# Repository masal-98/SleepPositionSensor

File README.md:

## Sleep position classifier
## Objective

The aim of this group project was to develop a system able to correctly classify and forecast **12 specific sleep positions** (visible in the image above), using the data from **two accelerometers LIS3DH** placed one on the chest and one on the right ankle. 
The finished project includes: 
- development of the wearable device
- data acquisition
- data processing
- GUI for data sampling and visualization
- machine learning architecture able to perform sleep position classification

The PSoC communicates with the LIS3DH sensors using **I2C communication**, and the accelerometers have a sampling frequency set at 10Hz. 
The communication between the PSoC device and the pc was created using a **HC05 Bluetooth module** to make the device wearable.
Also, for wearability, the device is powered with a **9V battery** and a subsequent **9 to 5 voltage transformer**.
### Hardware
- 2 LIS3DH accelerometers
- 1 HC05 Bluetooth module
- 1 9V battery
- 1 9to5 voltage transformer
- 1 PSoC CY8CKIT-059 
- 1 breadboard
- 2 3D printed casings were used to encapsulate the accelerometers and place them on the body
- 10 2m long cables to connect the accelerometers to the PSoC
- 2 modular velcro bands to fix the accelerometers in place 

The links between the PSoC and the different components can be found in the dedicated folder in the form of the **hardware** **setup** documentation and the eagle schematic and board files.
The casing's 3D model can also be found in the dedicated folder.

### PSoC code
This section of code is responsible for I2C communication between the PSoC and the 2 accelerometers, which are sampling data with an ODR of 10Hz and are set on **FIFO mode**. The following code averages the 32 samples of the FIFO buffer from both accelerometers, each time they are simultaneously full.
Finally, the 6 averaged acceleration values (x, y and z from the chest and the ankle) are combined in a unique string and managed by the **UART** of the bluetooth module, having a baudrate of 9600 bps.

All code files of this section have been individually commented on for clarity.

### GUI code

This section of code deals with establishing a connection between pc and bluetooth module, visualizing the data sampled in real-time, and producing csv files following a specific sampling protocol, which are further used to train the machine learning module. 
It follows a description of the most important subsections of code, but the code has been commented throughout for clarity.
#### $Serial$ $interface$
This subsection is devoted to scanning all serial ports and creating a list used in the dropdown menu.
#### $Serial$ $Worker$
The **SerialWorker** class handles the connection with the bluetooth module by establishing a connection with the desired serial port (selectable in a drop down menu), reading data from this port from start (S) to end (E) tokens as soon as the Start button is pressed, **storing iteratively** the read lines in the data object and saving them at the end of the protocol in a single csv file.  
It's also responsible for sending char data on the serial port and closing the serial port before closing the app.
#### $Graphic$ $interface$ 
This sub-section of code deals with creating the **window** used by all the plot widgets and the various **buttons**. 
It's worth noting that the 6 data charts are plotted on the same window by first removing the oldest point, then adding the new one, and finally updating the data.
#### $Main$
The main is responsible for setting the **window size**, creating the **thread handler** and **initializing** all the **functions** previously mentioned.

### Machine Learning
#### $Install$

The Machine Learning portion of this project was created using a Jupyter Notebook.
The library used are available in the *requirements.txt* file inside the *machine learning folder* and any function needed is clearly listed and commented troughout the code.

#### $Data$
In order to run the code, it's necessary to upload the csv files produced by us during the sampling. All the paths are stored in a distinct variable.

The data consists in 11 csv files sampled from 11 different people, it's worth nothing that the file 'fabio_20220601_193018.csv' was discarted 
due to errors during the sampling procedure, thus we ended up with 10 different people, a sample size big enough to guarantee inter-subject variabilty.

The data available was studied in three different ways, in order to see if the accuracy of the model could be improved:
- **Raw** sampled data
- **Average** of data for each sensor
- **Average** of data for each sensor + **minimun and maximum** values for each sensor

#### $Data Preprocessing$
It's important to note that the **first 20 samples of each position recording were removed**, due to the patient still not being completely settled down and ready for the sampling. 
The data was also **normalized** as good practice dictates.

#### $Data Visualization$
The data was visualized multiple times, this allowed us to purge it from artifacts and anomalies and improve the learning algorithm, such as the *transient
data* between two positions mentioned in the previous paragraph.

#### $Features$
The data was gathered from 2 accelerometers, one on the chest and one on the right ankle. Therefore we have 6 inputs + 1 input for the subject's sex.
- x_chest
- y_chest
- z_chest
- x_ankle
- y_ankle
- z_ankle
- sex

#### $Target Variable$
The variable that we need to predict is the sleeping position. It can be one of twelve positions.

##### $Run$
To run the code, simply run sequentially every data cell. 
The code was tested on all three datasets, and the best performing one turned out to be the **Random Forest Classifier** learned using the **average+min_max** dataset, which reached **50% of accuracy** on the test set.

#### $Master Position$
In order to better assess the performance of the classifier we also tested it only on the four "master" positions: by grouping by three the positions (and therefore eliminating the small variations between each of the main positions) we obtained the **main positions**: supine, prone, left-sided and right-sided. 
When we tested our algorithm only with these targets, we easily obtained **100% accuracy**.

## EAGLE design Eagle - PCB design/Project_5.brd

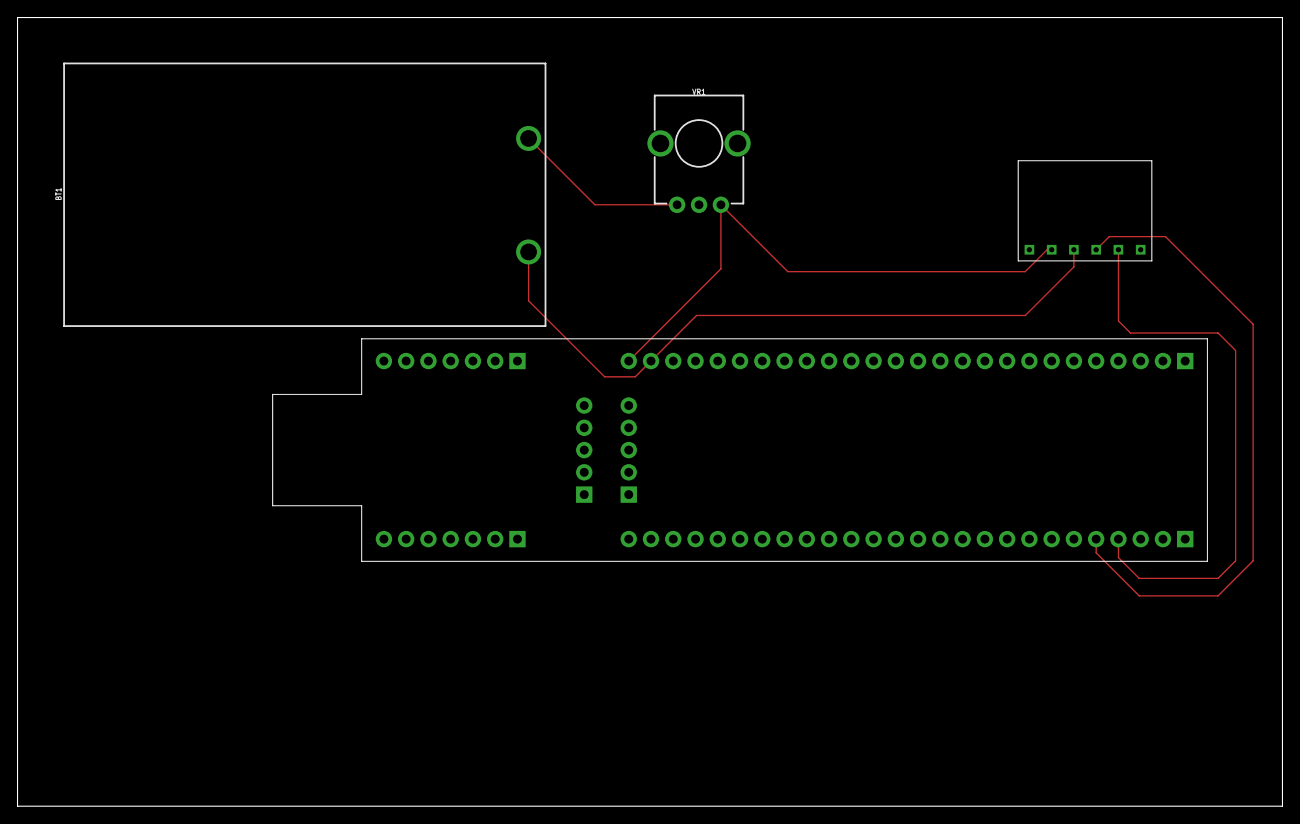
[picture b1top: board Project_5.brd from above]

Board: 2 copper layers, 144.3 x 90.0 mm, 4 parts (0 on the bottom side), 5 nets.

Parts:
BT1: BATTCON_9V
U$1: CY8CKIT-059
U$2: HC; HC-05
VR1: 10k; POT-PTH-ALPS-KIT

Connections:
unnamed: BT1.-, U$1.25, U$2.P$4
unnamed: U$1.30, U$2.P$2
unnamed: U$1.31, U$2.P$3
unnamed: U$1.26, U$2.P$5, VR1.P$3
unnamed: BT1.+, VR1.P$1

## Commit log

2023-08-21 README.md

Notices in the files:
parts and their libraries:
SparkFun-Batteries: Licensing: Creative Commons ShareAlike 4.0 International - https://creativecommons.org/licenses/by-sa/4.0
